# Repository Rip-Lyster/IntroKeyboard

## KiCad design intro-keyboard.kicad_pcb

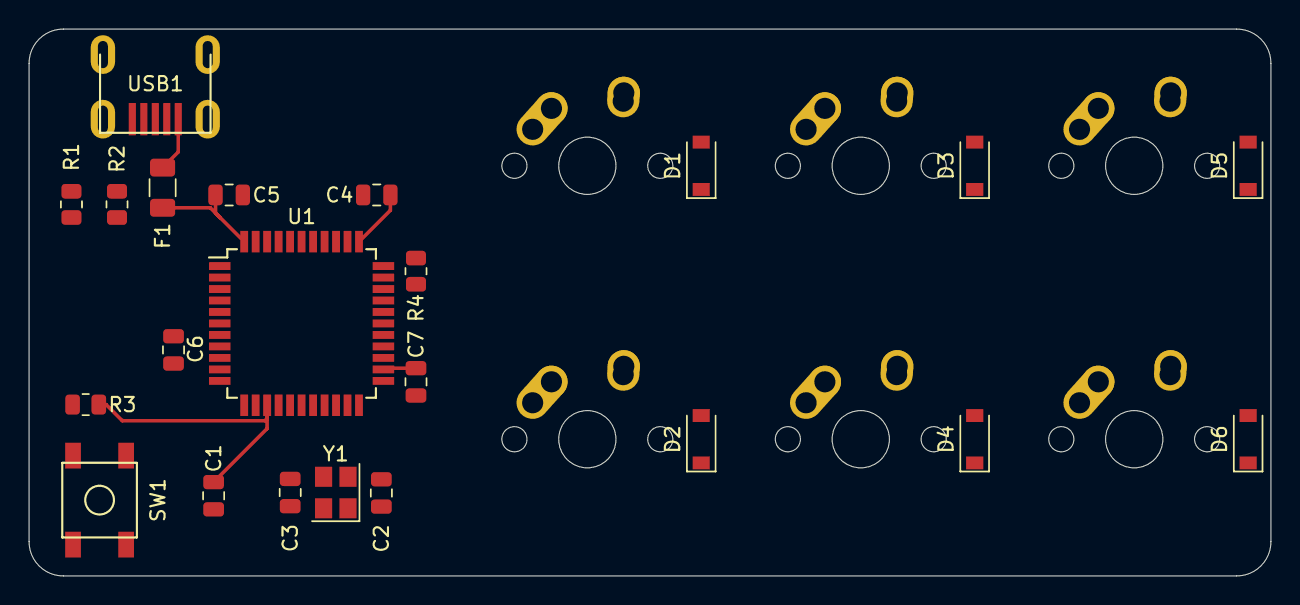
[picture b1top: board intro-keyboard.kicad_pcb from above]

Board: 2 copper layers, 86.5 x 38.1 mm, 28 parts (0 on the bottom side), 23 nets.

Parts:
C1, C4, C5: 0.1uF; C_0805_2012Metric
C2, C3: 22pF; C_0805_2012Metric
C6: 1uF; C_0805_2012Metric
C7: 10uF; C_0805_2012Metric
D1, D2, D3, D4, D5, D6: SOD-123; D_SOD-123
F1: 500mA; Fuse_1206_3216Metric
MX1, MX2, MX3, MX4, MX5, MX6: MX-NoLED; MX-1U-NoLED
R1, R2: 22; R_0805_2012Metric
R3, R4: 10k; R_0805_2012Metric
SW1: SW_Push; SKQG-1155865
U1: ATmega32U4-AU; TQFP-44_10x10mm_P0.8mm
USB1: Molex-0548190589
Y1: 16MHz; Crystal_SMD_3225-4Pin_3.2x2.5mm

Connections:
+5V: C1.1, C4.1, C5.1, C7.1, F1.1, R3.1, U1.2, U1.7, U1.14, U1.24, U1.34, U1.44
COL0: MX1.1, MX2.1
COL1: MX3.1, MX4.1
COL2: MX5.1, MX6.1
D+: R1.2, USB1.3
D-: R2.2, USB1.4
GND: C1.2, C2.2, C3.2, C4.2, C5.2, C6.2, C7.2, R4.1, SW1.1, U1.5, U1.15, U1.23, U1.35, U1.43, USB1.1, USB1.6, Y1.2, Y1.4
unnamed: C2.1, U1.17, Y1.1
unnamed: C3.1, U1.16, Y1.3
unnamed: C6.1, U1.6
unnamed: D1.2, MX1.2
unnamed: D2.2, MX2.2
unnamed: D3.2, MX3.2
unnamed: D4.2, MX4.2
unnamed: D5.2, MX5.2
unnamed: D6.2, MX6.2
unnamed: R1.1, U1.4
unnamed: R2.1, U1.3
unnamed: R3.2, SW1.2, U1.13
unnamed: R4.2, U1.33
ROW0: D1.1, D3.1, D5.1
ROW1: D2.1, D4.1, D6.1
VCC: F1.2, USB1.5

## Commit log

2021-04-10 adding all files
2021-04-11 adding components
2021-04-11 did some routing
